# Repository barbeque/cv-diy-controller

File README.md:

## Introduction

The stock "Hand Controller" on the ColecoVision is prone to wearing out. It is also uncomfortable to play for long periods of time, due to the position that your hand has to be placed into.

This PCB allows you to use a generic "arcade joystick kit" to build an arcade-style joystick for the ColecoVision. It makes it much easier to play.

## Version History
### 2024-v2
Diodes were flipped to actually make the PCB work properly. Mea culpa!

Board was shrunk below 100x100mm to make ordering cheaper.

## Support
If you liked this joystick, please [consider supporting my Patreon](https://www.patreon.com/leadedsolder) or [buying me a ko-fi](https://ko-fi.com/leadedsolder). Every penny goes back into making more free and open-source hardware for old computers and game systems.

## Ordering the PCB
Download the Gerber files from [the Releases page](/releases) and send them to your favourite PCB manufacturer.

You can also [order the PCB from PCBWay directly](https://www.pcbway.com/project/shareproject/ColecoVision_DIY_arcade_joystick_PCB_e30ae2ff.html); I will receive a small cut of this price.

## Bill of Materials

| Part                   | Quantity | Comment |
|------------------------|----------|---------|
| 1n5817 Schottky diode  | 28       | You can also use 1n4148, which is cheaper |
| A-DF 09 A/KG-T2S male DE9 | 1     | For use with a Sega extension cable.      |
| 0.1" male pin headers  | At least 40 | |

## Required Joystick Parts

In addition to the parts listed in the bill of materials, you will need to make sure that your joystick kit comes with buttons, and a Sanwa-style joystick.

The number pad can either be wired to individual buttons (I recommend wiring "1" and "*" at the very least) but some number pads will come with a multi-pin connector, which can then use the large connector on the side.

The female DE9 connector is meant to be used with a Sega Genesis controller extension cable, which is available on many sites like eBay and AliExpress. This will provide the correct pinout to the ColecoVision without having to do any messy cable-building, and you can keep the male end of the cable inside the joystick housing.

You can also wire your own cable into the 9-pin header in the middle of the board.

## Assembly

Break up your pin headers and solder them into the 2-pin connectors for number pad, ARM and FIRE buttons, and the joystick.

Fill every diode space with diodes. If you can't find 1n5817 Schottky diodes, it is OK to use the much more common (and cheaper) 1n4148.

Now it's time to assemble the joystick: put the case together according to the instructions that came with your joystick kit. Once that's done, remove the lid and install the PCB.

Check your joystick's connector. You may need to use a continuity test on your multimeter to figure out which pin is ground and which pins correspond to the directional microswitches. Make sure to install the stick the same way that the label on the board indicates.

Buttons can be connected to the 2-pin pin headers in either orientation: they are not polarized.

## Testing

The best game to test this joystick with is Frenzy, because it has some challenging diagonal directions in order to aim and fire around corners.

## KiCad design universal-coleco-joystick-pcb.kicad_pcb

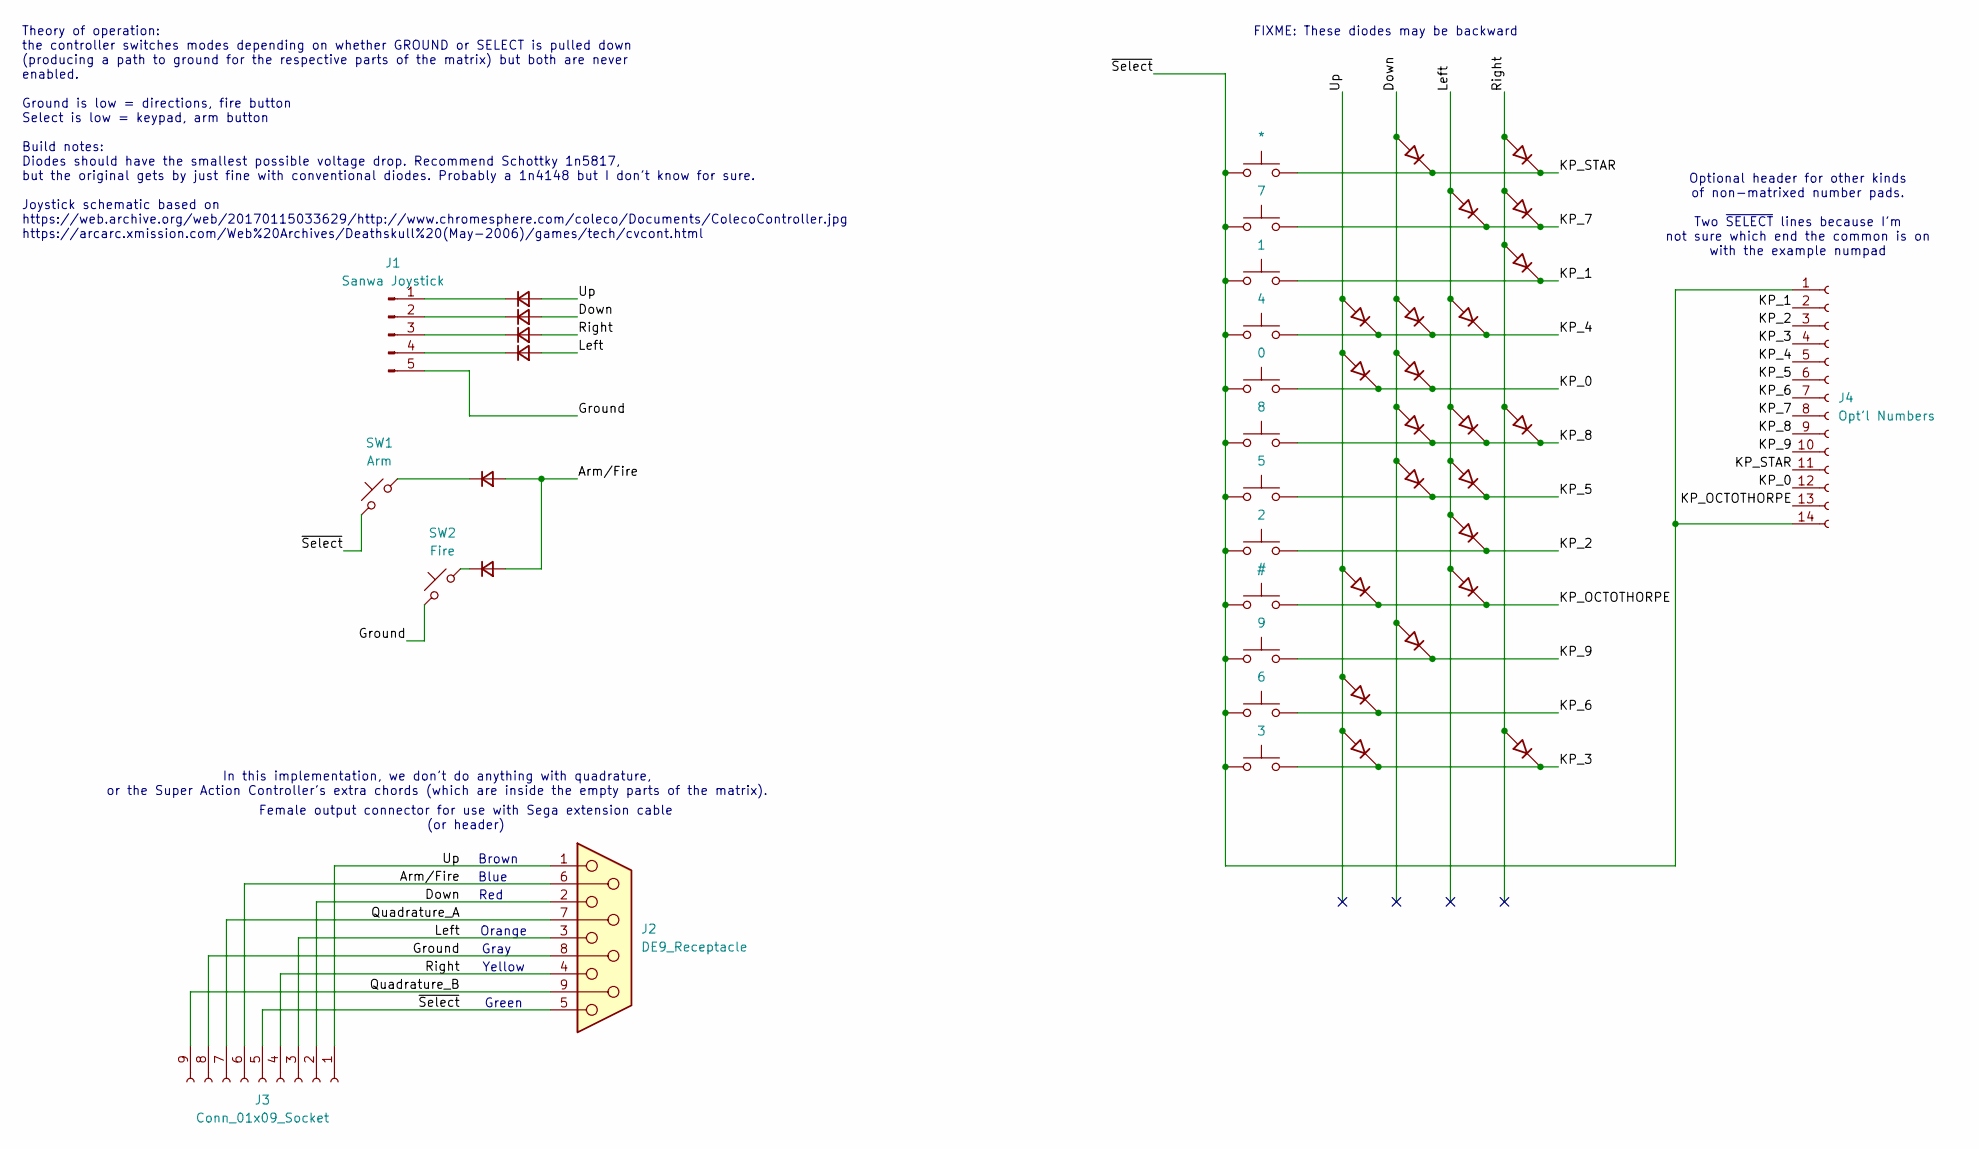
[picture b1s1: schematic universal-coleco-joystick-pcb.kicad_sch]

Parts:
D1, D2, D3, D4, D5, D6: D_Small; D_DO-41_SOD81_P10.16mm_Horizontal
D7, D8, D9, D10, D11, D12, D13, D14, D15, D16, D17, D18, D19, D20, D21, D22, D23, D24, D25, D26, D27, D28: D_45deg; D_DO-41_SOD81_P10.16mm_Horizontal
J1: Sanwa Joystick; PinHeader_1x05_P2.54mm_Vertical
J2: DE9_Receptacle; DSUB-9_Female_Horizontal_P2.77x2.84mm_EdgePinOffset7.70mm_H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
J3: Conn_01x09_Socket; PinHeader_1x09_P2.54mm_Vertical
J4: Opt'l Numbers; PinHeader_1x14_P2.54mm_Vertical
SW1: Arm; PinHeader_1x02_P2.54mm_Vertical
SW2: Fire; PinHeader_1x02_P2.54mm_Vertical
SW3: *; PinHeader_1x02_P2.54mm_Vertical
SW4: 7; PinHeader_1x02_P2.54mm_Vertical
SW5: 1; PinHeader_1x02_P2.54mm_Vertical
SW6: 4; PinHeader_1x02_P2.54mm_Vertical
SW7: 0; PinHeader_1x02_P2.54mm_Vertical
SW8: 8; PinHeader_1x02_P2.54mm_Vertical
SW9: 5; PinHeader_1x02_P2.54mm_Vertical
SW10: 2; PinHeader_1x02_P2.54mm_Vertical
SW11: #; PinHeader_1x02_P2.54mm_Vertical
SW12: 9; PinHeader_1x02_P2.54mm_Vertical
SW13: 6; PinHeader_1x02_P2.54mm_Vertical
SW14: 3; PinHeader_1x02_P2.54mm_Vertical

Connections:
/Arm/Fire: D5.2 (A), D6.2 (A), J2.6, J3.6
/Down: D2.2 (A), D7.2 (A), D13.2 (A), D16.2 (A), D17.2 (A), D20.2 (A), D25.2 (A), J2.2, J3.2
/Ground: J1.5, J2.8, J3.8, SW2.2
/KP_0: D15.1 (K), D16.1 (K), J4.12, SW7.2
/KP_1: D11.1 (K), J4.2, SW5.2
/KP_2: D22.1 (K), J4.3, SW10.2
/KP_3: D27.1 (K), D28.1 (K), J4.4, SW14.2
/KP_4: D12.1 (K), D13.1 (K), D14.1 (K), J4.5, SW6.2
/KP_5: D20.1 (K), D21.1 (K), J4.6, SW9.2
/KP_6: D26.1 (K), J4.7, SW13.2
/KP_7: D9.1 (K), D10.1 (K), J4.8, SW4.2
/KP_8: D17.1 (K), D18.1 (K), D19.1 (K), J4.9, SW8.2
/KP_9: D25.1 (K), J4.10, SW12.2
/KP_OCTOTHORPE: D23.1 (K), D24.1 (K), J4.13, SW11.2
/KP_STAR: D7.1 (K), D8.1 (K), J4.11, SW3.2
/Left: D4.2 (A), D9.2 (A), D14.2 (A), D18.2 (A), D21.2 (A), D22.2 (A), D24.2 (A), J2.3, J3.3
/Quadrature_A: J2.7, J3.7
/Quadrature_B: J2.9, J3.9
/Right: D3.2 (A), D8.2 (A), D10.2 (A), D11.2 (A), D19.2 (A), D28.2 (A), J2.4, J3.4
/Up: D1.2 (A), D12.2 (A), D15.2 (A), D23.2 (A), D26.2 (A), D27.2 (A), J2.1, J3.1
/~Select: J2.5, J3.5, J4.1, J4.14, SW1.2, SW3.1, SW4.1, SW5.1, SW6.1, SW7.1, SW8.1, SW9.1, SW10.1, SW11.1, SW12.1, SW13.1, SW14.1
unnamed: D1.1 (K), J1.1
unnamed: D2.1 (K), J1.2
unnamed: D3.1 (K), J1.3
unnamed: D4.1 (K), J1.4
unnamed: D5.1 (K), SW1.1
unnamed: D6.1 (K), SW2.1

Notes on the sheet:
Optional header for other kinds of non-matrixed number pads. Two ~{SELECT} lines because I'm not sure which end the common is on with the example numpad
Theory of operation: the controller switches modes depending on whether GROUND or SELECT is pulled down (producing a path to ground for the respective parts of the matrix) but both are never enabled. Ground is low = directions, fire button Select is low = keypad, arm button Build notes: Diodes shou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
Green
Blue
Brown
Female output connector for use with Sega extension cable (or header)
Red
In this implementation, we don't do anything with quadrature, or the Super Action Controller's extra chords (which are inside the empty parts of the matrix).
FIXME: These diodes may be backward
Yellow
Gray
Orange

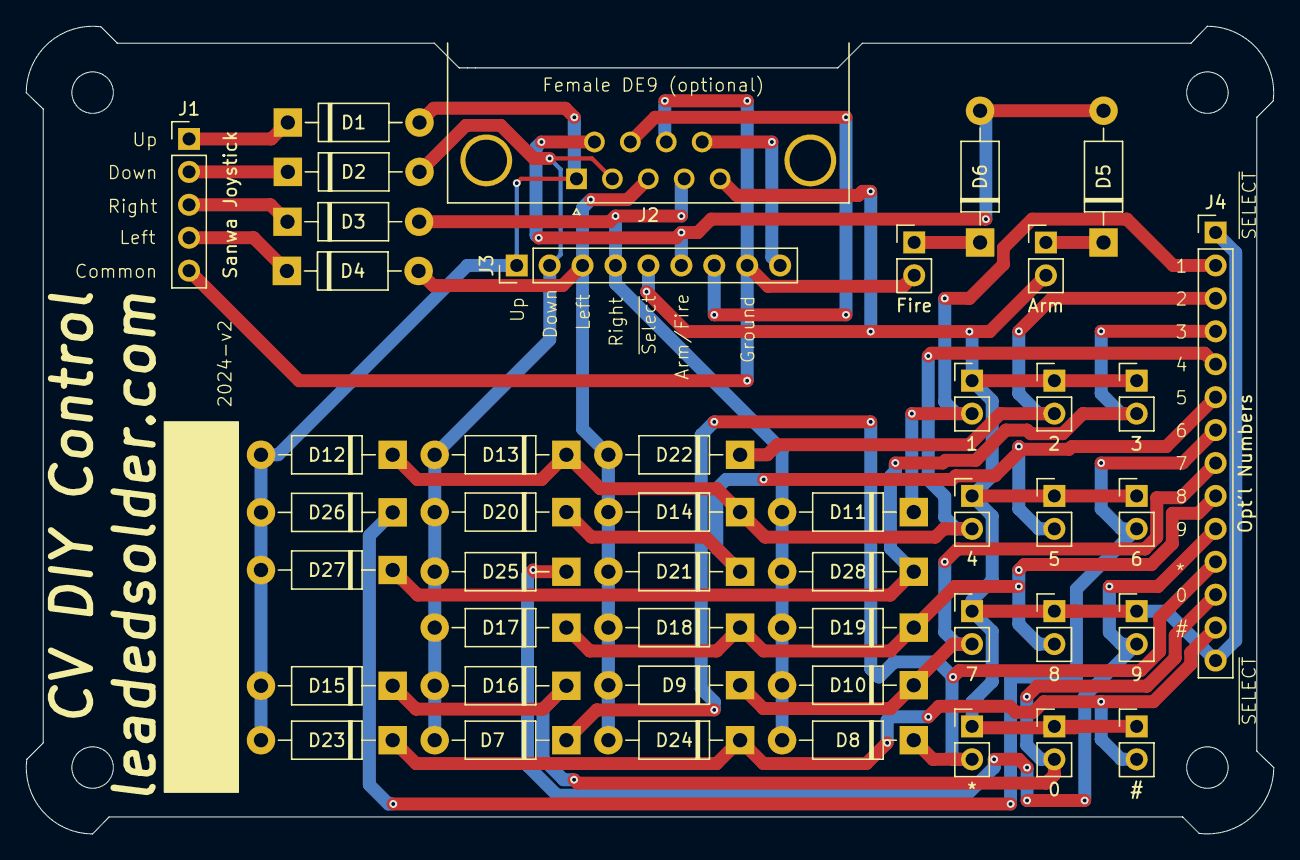
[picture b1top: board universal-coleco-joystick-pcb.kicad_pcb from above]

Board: 2 copper layers, 96.2 x 62.3 mm, 46 parts (0 on the bottom side), 27 nets.

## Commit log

2024-06-26 Schematic hashed out
2024-06-26 Diode soup
2024-06-26 Fix unsightly labels
2024-06-26 Credit
2024-06-27 Linear KP header
2024-07-01 Release v1 to JLC
2024-07-02 Step export
2024-07-21 Warning: Diodes may be backward for number matrix
2024-08-26 UDRL not UDLR joystick error
2024-08-27 Diodes flipped, board shrunk below 100x100
2024-10-03 README
2024-10-03 Github funding
2024-10-03 How to order
2025-12-23 Version history update
